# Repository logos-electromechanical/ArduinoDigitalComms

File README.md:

# ArduinoDigitalComms
Class files for Digital Communications with Arduino workshop at Metrix

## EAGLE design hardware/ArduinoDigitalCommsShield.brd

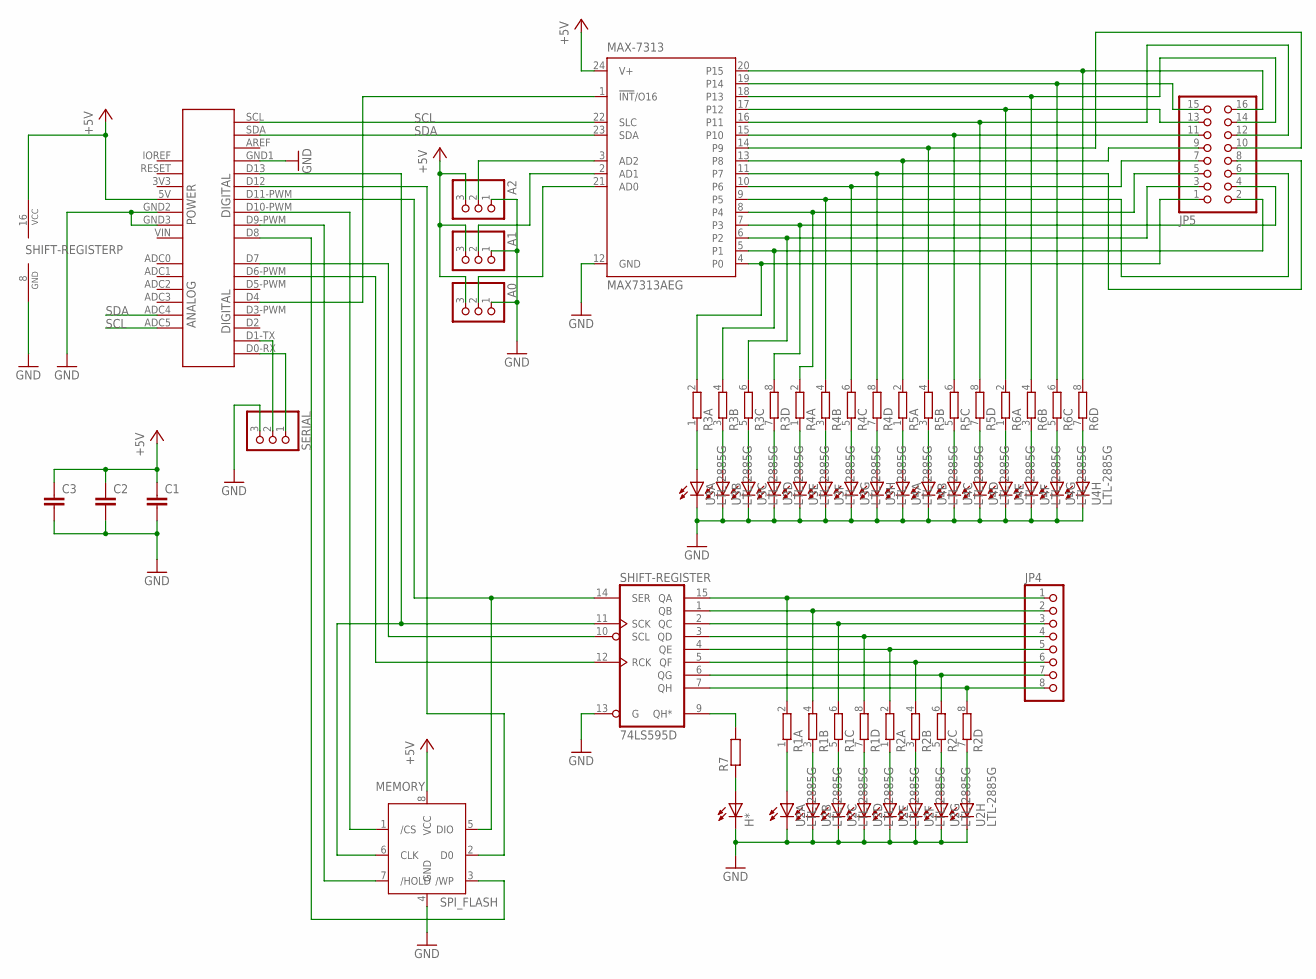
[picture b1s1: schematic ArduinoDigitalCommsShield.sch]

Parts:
A0, A1, A2: PINHD-1X3_2.54; 1X03
ARD1: UNO-R3
C1, C2, C3: C-EUC0603; C0603
H*: LED5MM
JP4: PINHD-1X8_2.54; 1X08
JP5: PINHD-2X8_2.54; 2X08
MAX-7313: MAX7313AEG; QSOP24
MEMORY: SPI_FLASH; SOIC-8
R1, R2, R3, R4, R5, R6: 4R-NCTS742C083; CTS742C083-RES
R7: R-EU_R0603; R0603
SERIAL: PINHD-1X3_2.54; 1X03
SHIFT-REGISTER: 74LS595D; SO16
U2, U3, U4: LTL-2885G; LTL-2*85

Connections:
+5V: A0.3, A1.3, A2.3, ARD1.5V, C1.1, C2.1, C3.1, MAX-7313.24 (V+), MEMORY.8 (VCC), SHIFT-REGISTER.16 (VCC)
GND: A0.1, A1.1, A2.1, ARD1.GND1, ARD1.GND2, ARD1.GND3, C1.2, C2.2, C3.2, H*.K (C), MAX-7313.12 (GND), MEMORY.4 (GND), SERIAL.3, SHIFT-REGISTER.8 (GND), SHIFT-REGISTER.13 (G), U2.1 (C), U2.4 (C), U2.5 (C), U2.8 (C), U2.9 (C), U2.12 (C), U2.13 (C), U2.16 (C), U3.1 (C), U3.4 (C), U3.5 (C), U3.8 (C), U3.9 (C), U3.12 (C), U3.13 (C), U3.16 (C), U4.1 (C), U4.4 (C), U4.5 (C), U4.8 (C), U4.9 (C), U4.12 (C), U4.13 (C), U4.16 (C)
unnamed: A2.2, MAX-7313.3 (AD2)
unnamed: A1.2, MAX-7313.2 (AD1)
unnamed: A0.2, MAX-7313.21 (AD0)
unnamed: ARD1.D11-PWM (D11), MEMORY.5 (DIO), SHIFT-REGISTER.14 (SER)
unnamed: ARD1.D13, MEMORY.6 (CLK), SHIFT-REGISTER.11 (SCK)
unnamed: ARD1.D7, SHIFT-REGISTER.10 (SCL)
unnamed: ARD1.D6-PWM (D6), SHIFT-REGISTER.12 (RCK)
unnamed: ARD1.D4, MAX-7313.1 (!INT!/O16)
unnamed: JP4.1, R1.2, SHIFT-REGISTER.15 (QA)
unnamed: JP4.2, R1.4 (2), SHIFT-REGISTER.1 (QB)
unnamed: JP4.3, R1.6 (2), SHIFT-REGISTER.2 (QC)
unnamed: JP4.4, R1.8 (2), SHIFT-REGISTER.3 (QD)
unnamed: JP4.5, R2.2, SHIFT-REGISTER.4 (QE)
unnamed: JP4.6, R2.4 (2), SHIFT-REGISTER.5 (QF)
unnamed: JP4.7, R2.6 (2), SHIFT-REGISTER.6 (QG)
unnamed: JP4.8, R2.8 (2), SHIFT-REGISTER.7 (QH)
unnamed: JP5.1, MAX-7313.4 (P0), R3.2
unnamed: JP5.2, MAX-7313.5 (P1), R3.4 (2)
unnamed: JP5.3, MAX-7313.6 (P2), R3.6 (2)
unnamed: JP5.4, MAX-7313.7 (P3), R3.8 (2)
unnamed: JP5.5, MAX-7313.8 (P4), R4.2
unnamed: JP5.6, MAX-7313.9 (P5), R4.4 (2)
unnamed: JP5.7, MAX-7313.10 (P6), R4.6 (2)
unnamed: JP5.8, MAX-7313.11 (P7), R4.8 (2)
unnamed: JP5.16, MAX-7313.20 (P15), R6.8 (2)
unnamed: JP5.15, MAX-7313.19 (P14), R6.6 (2)
unnamed: JP5.14, MAX-7313.18 (P13), R6.4 (2)
unnamed: JP5.13, MAX-7313.17 (P12), R6.2
unnamed: JP5.12, MAX-7313.16 (P11), R5.8 (2)
unnamed: JP5.11, MAX-7313.15 (P10), R5.6 (2)
unnamed: JP5.10, MAX-7313.14 (P9), R5.4 (2)
unnamed: JP5.9, MAX-7313.13 (P8), R5.2
unnamed: ARD1.D10-PWM (D10), MEMORY.1 (/CS)
unnamed: ARD1.D12, MEMORY.2 (D0)
unnamed: ARD1.D9-PWM (D9), MEMORY.7 (/HOLD)
unnamed: ARD1.D8, MEMORY.3 (/WP)
unnamed: ARD1.D1-TX (D1), SERIAL.2
unnamed: ARD1.D0-RX (D0), SERIAL.1
unnamed: H*.A, R7.1
unnamed: R7.2, SHIFT-REGISTER.9 (QH*)
unnamed: R1.1, U2.2 (A)
unnamed: R1.3 (1), U2.3 (A)
unnamed: R1.5 (1), U2.6 (A)
unnamed: R1.7 (1), U2.7 (A)
unnamed: R2.1, U2.10 (A)
unnamed: R2.3 (1), U2.11 (A)
unnamed: R2.5 (1), U2.14 (A)
unnamed: R2.7 (1), U2.15 (A)
unnamed: R3.1, U3.2 (A)
unnamed: R3.3 (1), U3.3 (A)
unnamed: R3.5 (1), U3.6 (A)
unnamed: R3.7 (1), U3.7 (A)
unnamed: R4.1, U3.10 (A)
unnamed: R4.3 (1), U3.11 (A)
unnamed: R4.5 (1), U3.14 (A)
unnamed: R4.7 (1), U3.15 (A)
unnamed: R5.1, U4.2 (A)
unnamed: R5.3 (1), U4.3 (A)
unnamed: R5.5 (1), U4.6 (A)
unnamed: R5.7 (1), U4.7 (A)
unnamed: R6.1, U4.10 (A)
unnamed: R6.3 (1), U4.11 (A)
unnamed: R6.5 (1), U4.14 (A)
unnamed: R6.7 (1), U4.15 (A)
SCL: ARD1.ADC5, ARD1.SCL, MAX-7313.22 (SLC)
SDA: ARD1.ADC4, ARD1.SDA, MAX-7313.23 (SDA)

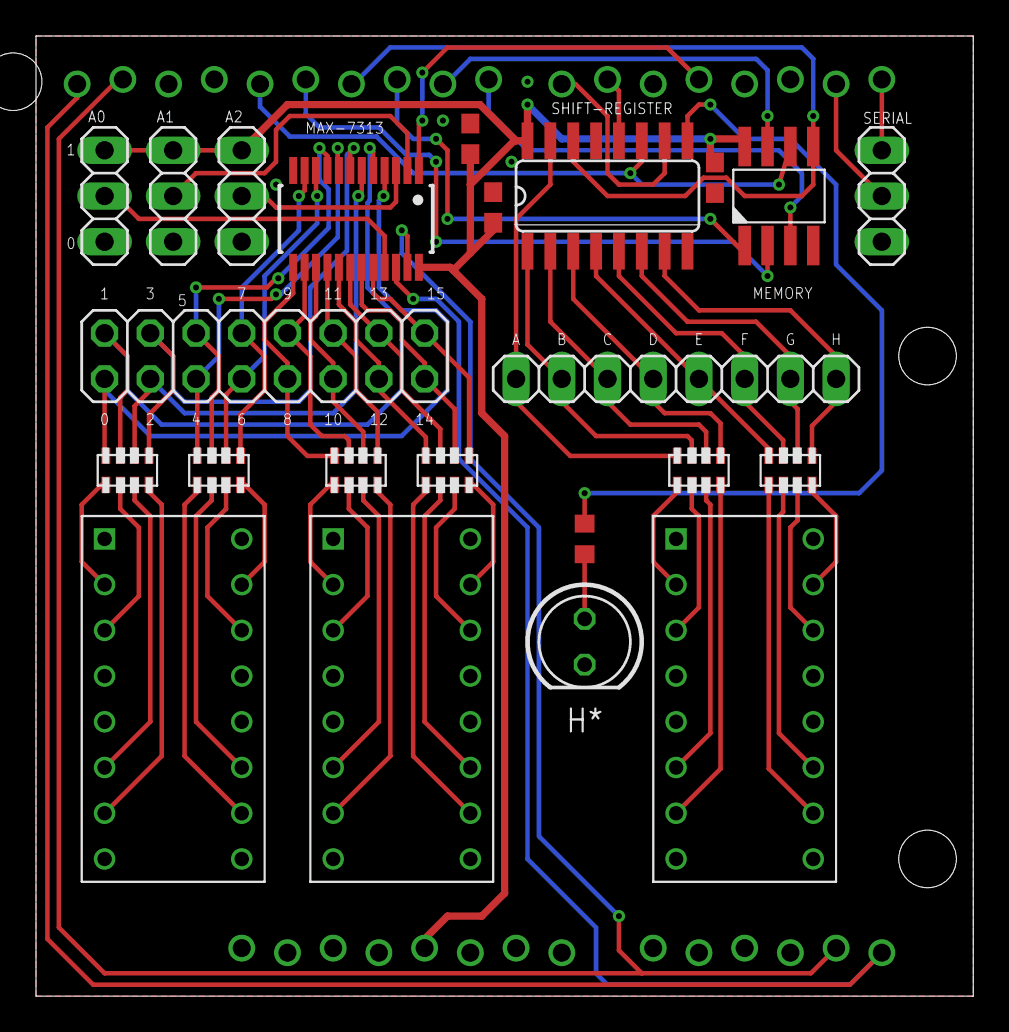
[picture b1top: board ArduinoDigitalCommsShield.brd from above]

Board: 2 copper layers, 52.1 x 53.3 mm, 24 parts (0 on the bottom side), 68 nets.

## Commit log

2015-02-28 First check-in
2015-02-28 final commit before class
